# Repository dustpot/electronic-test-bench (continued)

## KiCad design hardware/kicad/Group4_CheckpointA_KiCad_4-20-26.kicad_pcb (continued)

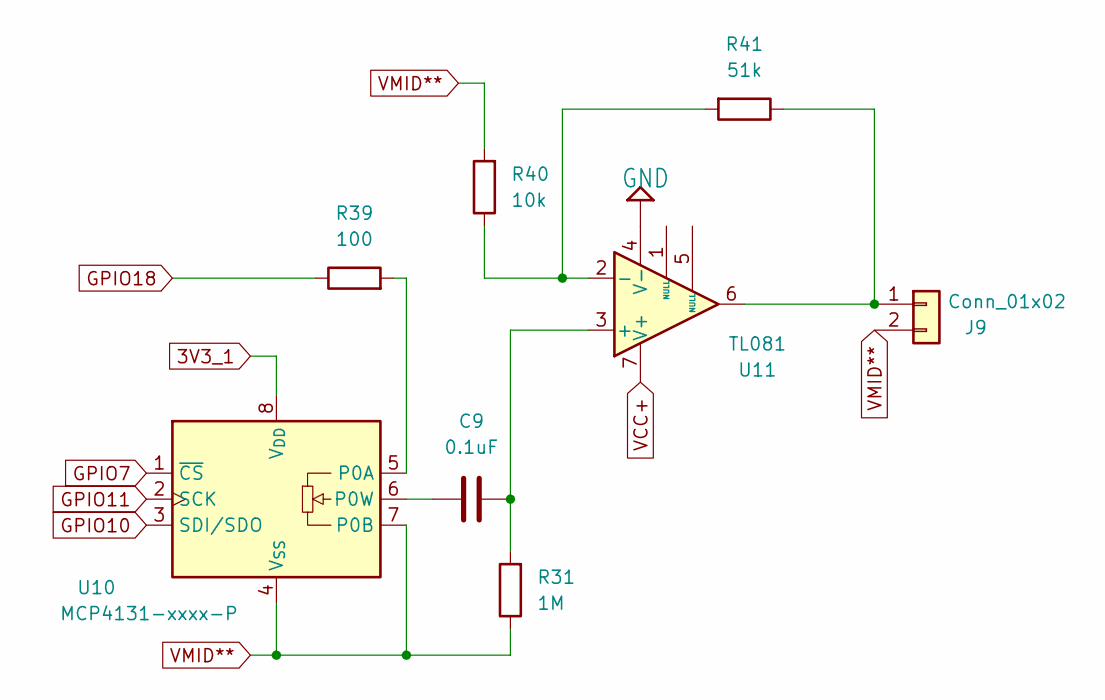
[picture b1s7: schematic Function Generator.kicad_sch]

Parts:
C9: 0.1uF; C_Disc_D5.0mm_W2.5mm_P2.50mm
J9: Conn_01x02; PinHeader_1x02_P2.54mm_Vertical
R31: 1M; R_Axial_DIN0207_L6.3mm_D2.5mm_P2.54mm_Vertical
R39: 100; R_Axial_DIN0207_L6.3mm_D2.5mm_P2.54mm_Vertical
R40: 10k; R_Axial_DIN0207_L6.3mm_D2.5mm_P2.54mm_Vertical
R41: 51k; R_Axial_DIN0207_L6.3mm_D2.5mm_P2.54mm_Vertical
U10: MCP4131-xxxx-P; DIP-8_W7.62mm
U11: TL081; DIP-8_W7.62mm

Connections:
3V3_1: U10.8 (V_{DD}); also elsewhere on the board
-12: U11.4 (V-); also elsewhere on the board
GPIO7: U10.1 (~CS); also elsewhere on the board
GPIO10: U10.3 (SDI/SDO); also elsewhere on the board
GPIO11: U10.2 (SCK); also elsewhere on the board
GPIO18: R39.1; also elsewhere on the board
unnamed: J9.1, R41.1, U11.6
unnamed: R39.2, U10.5 (P0A)
unnamed: C9.1, U10.6 (P0W)
unnamed: C9.2, R31.2, U11.3 (+)
unnamed: R40.1, R41.2, U11.2 (-)
VCC+: U11.7 (V+); also elsewhere on the board
VMID**: J9.2, R31.1, R40.2, U10.4 (V_{SS}), U10.7 (P0B); also elsewhere on the board

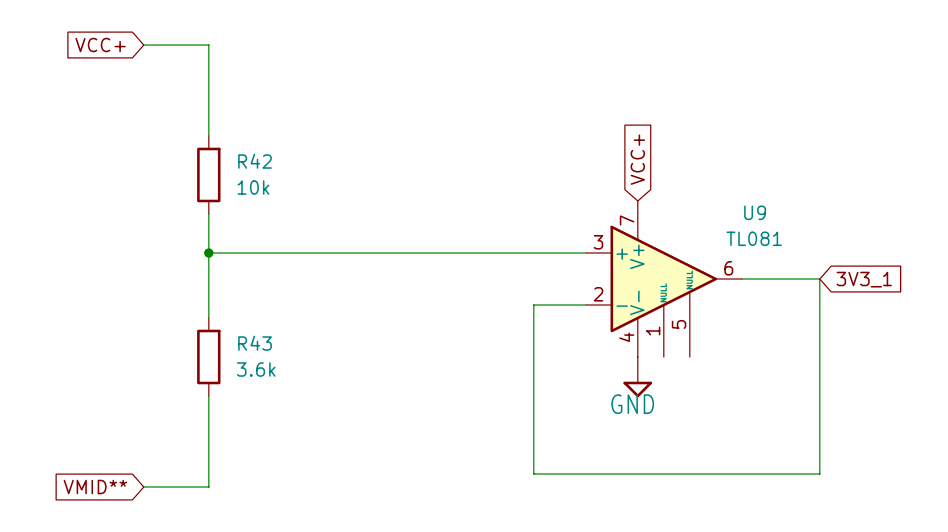
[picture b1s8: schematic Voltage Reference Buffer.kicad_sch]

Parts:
R42: 10k; R_Axial_DIN0207_L6.3mm_D2.5mm_P2.54mm_Vertical
R43: 3.6k; R_Axial_DIN0207_L6.3mm_D2.5mm_P2.54mm_Vertical
U9: TL081; DIP-8_W7.62mm

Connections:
3V3_1: U9.2 (-), U9.6; also elsewhere on the board
-12: U9.4 (V-); also elsewhere on the board
unnamed: R42.1, R43.2, U9.3 (+)
VCC+: R42.2, U9.7 (V+); also elsewhere on the board
VMID**: R43.1; also elsewhere on the board

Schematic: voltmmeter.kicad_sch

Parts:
C3: 0.1uF; C_Disc_D5.0mm_W2.5mm_P2.50mm
J6: Conn_01x02; PinHeader_1x02_P2.54mm_Vertical
R2, R3: 10k; R_Axial_DIN0207_L6.3mm_D2.5mm_P2.54mm_Vertical
R10, R11: 1M; R_Axial_DIN0207_L6.3mm_D2.5mm_P2.54mm_Vertical
R25, R27, R28: 100k; R_Axial_DIN0207_L6.3mm_D2.5mm_P2.54mm_Vertical
R45: 33k; R_Axial_DIN0207_L6.3mm_D2.5mm_P2.54mm_Vertical
U3: TL084CN; DIP-14_W7.62mm

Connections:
3V3_1: R2.1; also elsewhere on the board
-12: U3.11 (VCC-); also elsewhere on the board
unnamed: C3.1, R2.2, R3.2, R10.1
unnamed: J6.1, R28.2
unnamed: R28.1, R45.2, U3.6 (2IN-)
unnamed: R27.2, R45.1, U3.7 (2OUT)
unnamed: R10.2, R11.2, U3.10 (3IN+)
unnamed: R25.2, R27.1, U3.9 (3IN-)
VCC+: U3.4 (VCC+); also elsewhere on the board
VMID**: C3.2, J6.2, R3.1, R11.1, U3.5 (2IN+); also elsewhere on the board
VM_OUT: R25.1, U3.8 (3OUT); also elsewhere on the board

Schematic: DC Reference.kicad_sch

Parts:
C4: 1u; CP_Radial_D10.0mm_P5.00mm
C6, C8: .1u; C_Disc_D5.0mm_W2.5mm_P5.00mm
J10: Conn_01x02; PinHeader_1x02_P2.54mm_Vertical
R32: 1.37k; R_Axial_DIN0207_L6.3mm_D2.5mm_P2.54mm_Vertical
R33, R38: 1k; R_Axial_DIN0207_L6.3mm_D2.5mm_P2.54mm_Vertical
R34, R35: 33k; R_Axial_DIN0207_L6.3mm_D2.5mm_P2.54mm_Vertical
R36, R37: 127k; R_Axial_DIN0207_L6.3mm_D2.5mm_P2.54mm_Vertical
U1: TL071; DIP-8_W7.62mm

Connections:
3V3_1: R32.1; also elsewhere on the board
-12: U1.4 (V-); also elsewhere on the board
unnamed: C4.1, C6.2, R32.2, R33.2, R34.1
unnamed: C8.1, J10.1, R38.2
unnamed: R37.1, R38.1, U1.6
unnamed: R35.2, R36.1, U1.3 (+)
unnamed: R34.2, R37.2, U1.2 (-)
VCC+: U1.7 (V+); also elsewhere on the board
VDAC: R35.1; also elsewhere on the board
VMID**: C4.2, C6.1, C8.2, J10.2, R33.1, R36.2; also elsewhere on the board

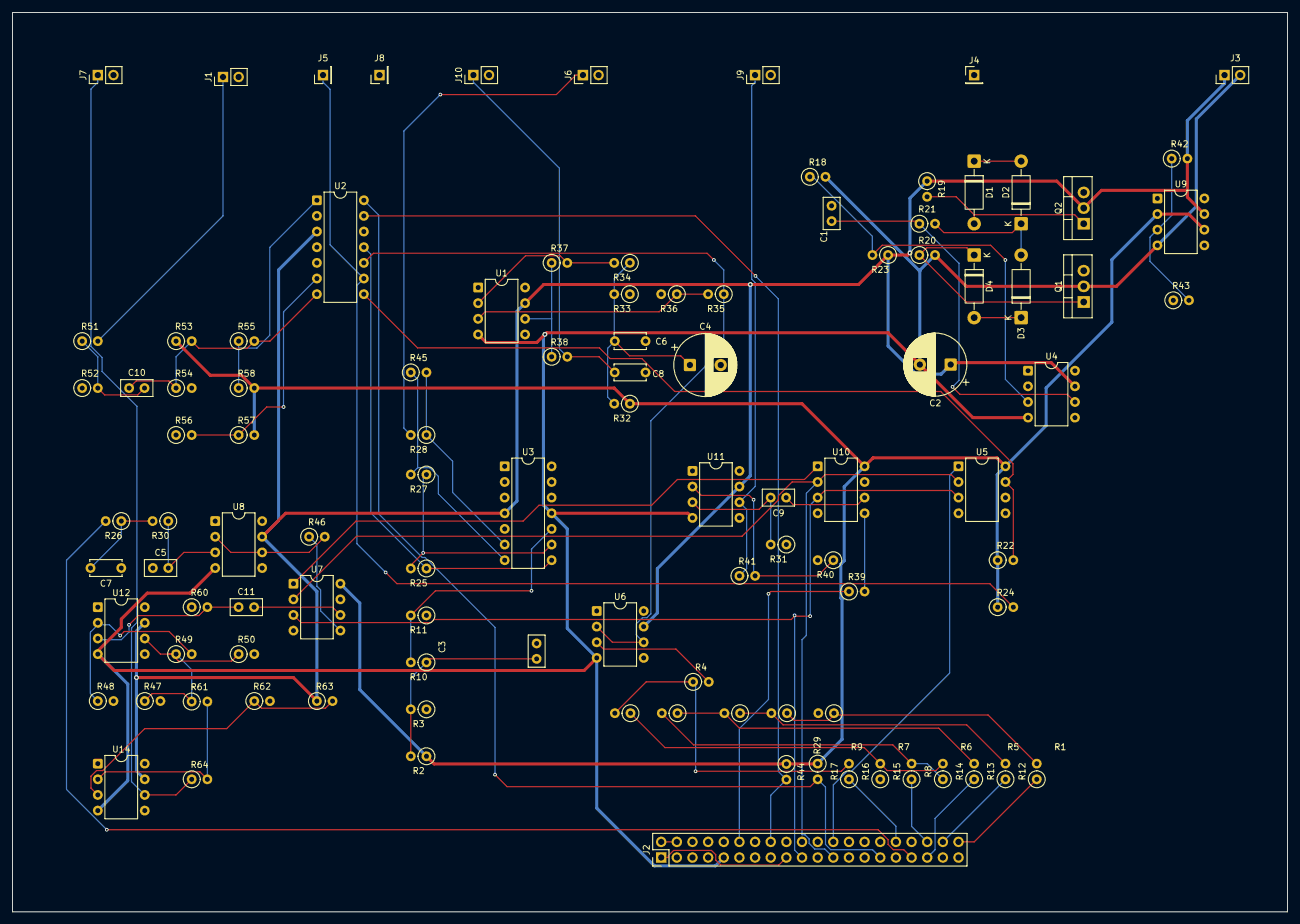
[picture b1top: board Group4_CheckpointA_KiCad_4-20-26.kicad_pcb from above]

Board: 2 copper layers, 206.9 x 146.0 mm, 103 parts (0 on the bottom side), 70 nets.
